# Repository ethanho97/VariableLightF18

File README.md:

# Design Skills Project (Variable Light Intensity)

## About

This project is meant to train our design skills by working out an entire design process to make a variable LED. By the end of the Fall 2018 semester, we will have made a variable LED light with the following specifications and constraints. This project will have us work individually to come up with our own design and planning process which will be maintained via this repository.

## Functional Specifications
* LED light that is button-activated to switch between the following operating modes:
  1. `Off`
  1. `Brightest`
  1. `Intermediate Brightness`
  1. `Least Bright`
  1. `Flashing @ 2 Hz`
* Self-contained device with LED and button exposed.
* Extra credit possibilities:
  + Battery life indicator
  + Waterproof enclosure
  + You tell us!

## Constraints
* Run on single battery up to 9 V
* Electronics connected to a single PCB (can be single- or double-sided)
* Cannot weight more than 1 lb
* Cannot have a single dimension > 6 in
* Cannot cost more than $50 to duplicate unit
* Battery must be easily replaceable

## Evaluation
* Minimize weight
* Minimize size
* Maximize `Brightest` mode
* Minimize power draw / maximize battery life
* Survive 3 foot drop with battery installed

* Create-and-maintain a GitHub project repository to maintain version history of:
  + Mechanical CAD (PDFs + more)
  + Electronic CAD (PDFs + more)
  + Software
  + Testing data
  + Design history / notes
  + Specification sheets
  + Usage notes (`README.md`)
  + Kanban board / Issues / Milestones

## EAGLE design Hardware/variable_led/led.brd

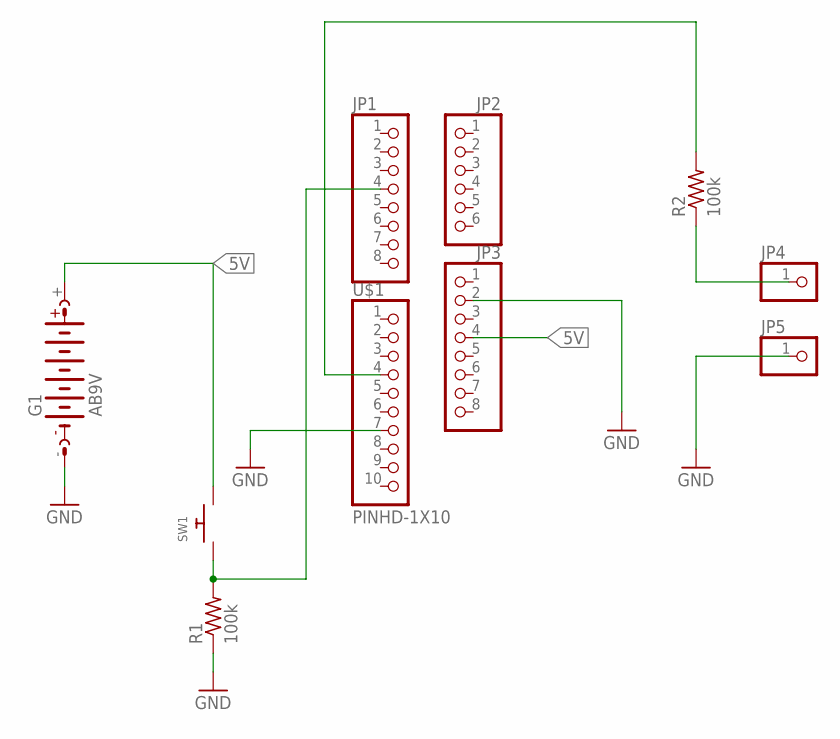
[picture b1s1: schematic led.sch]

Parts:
G1: AB9V
JP1, JP3: PINHD-1X8BIG; 1X08-BIG
JP2: PINHD-1X6B; 1X06-BIG
JP4, JP5: PINHD-1X1; 1X01
R1, R2: 100k; 0805-THM
SW1: SWITCH_PUSHBUTTONSOFTTOUCHSMD_SJ; PUSHBUTTON_SMD_SJ
U$1: PINHD-1X10; 1X10-BIG

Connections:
5V: G1.+, JP3.4, SW1.P$2
GND: G1.-, JP3.2, JP5.1, R1.1, U$1.7
unnamed: R2.2, U$1.4
unnamed: JP4.1, R2.1
unnamed: JP1.4, R1.2, SW1.P$1

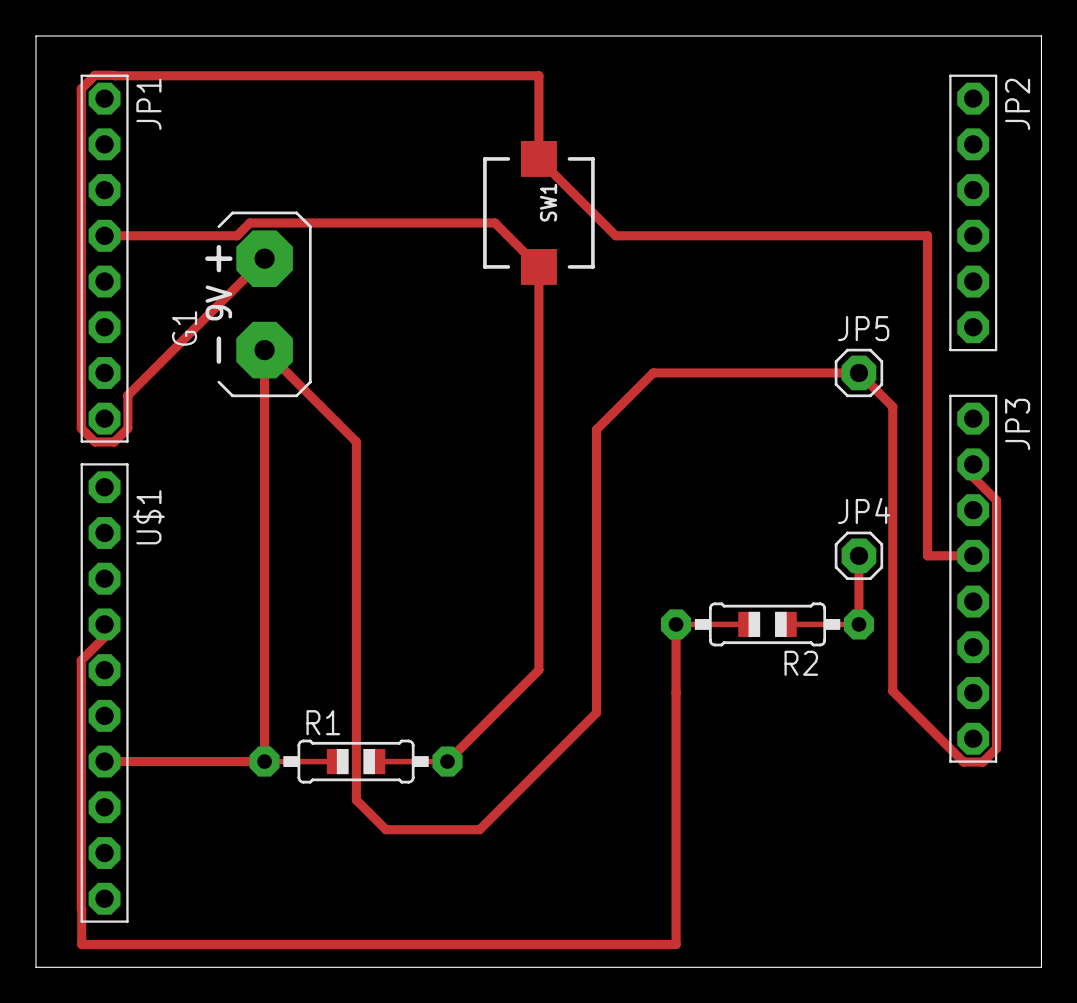
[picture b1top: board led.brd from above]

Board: 2 copper layers, 55.9 x 51.7 mm, 10 parts (0 on the bottom side), 5 nets.

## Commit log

2018-09-20 Fixed typo
2018-10-02 Added functional block diagram
2018-10-02 Removed transparent background for readability
2018-10-02 Testing authentication
2018-10-02 Added initial sketches for design
2018-11-01 Ignore .idea directory
2018-11-01 Added pseudocode
2018-11-01 Added schematics
2018-11-08 Added finalized schematic and PCB design
2018-11-16 Updated schematic labels and PCB layout based on feedback
2018-11-19 Initial case CAD
2018-11-28 Ignores eagle back ups
2018-11-28 Updated schematics without the voltage regulator
2018-11-28 Updated PCB based on feedback
2018-11-28 Started work on changing the hinges
2018-11-28 Updated back ups
2018-11-29 Breaking CAD into separate parts
2018-11-29 Updated EDA backups
2018-11-29 Ignores temporary solidworks files
2018-11-29 Added hinges to pcb box
2018-11-29 Made battery case into a separate part and added hinges
2018-11-30 Changed LED to two pins and changed board to single side
2018-12-13 Updated lid design and added battery compartment
2018-12-13 Created light lid
2018-12-13 Updated extrude names
2018-12-13 Updated arduino code
2018-12-13 Updated electronics (old)
2018-12-13 Updated methods and variable names so this is no longer pseudo-code
2018-12-13 Fixed setting correct operation mode and added debouncing to buttons
2018-12-13 Added slt files and formatted gcode ready for printing
2018-12-14 Updated code
2018-12-14 Resized case parts
2018-12-14 Updated print ready version of CAD
